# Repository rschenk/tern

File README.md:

# Tern

Terns are small white seabirds that can hover, but it's also a 30-key keyboard based on the [Hummingbird](https://github.com/PJE66/hummingbird)! Differences from the Hummigbird:

* Hot swappable
* Spaced for Chosfox CFX keycaps (tighter than normal choc spacing)
* Pinky keys are dropped down
* Thumbs are more reachy

I much prefer reachy thumbs vs tucky thumbs. Years of wiping out on skateboards means my right thumb doesn’t really make that tucking motion anymore.

The other deviation from the hummingbird is that I’m using the upper pinky key as my homerow. I’m using my pinky column as home and bottom rows, not top and home rows like the hummingbird does. Cognitively I like the hummingbird’s solution better, but after cutting a stack of cardboard prototypes, I just had to admit to myself that my pinky does not enjoy extending upwards.

## Case

There are laser cutting files for a case in `case`. The switch plate is made from 1/16" acrylic, and there is a 0.6mm silicone gasket sitting between it and the PCB. I don't actually think the switchplate does anything functional but it looks more finished. There is a file for cutting a sheet of self-adhesive foam for the back which really helps to dampen the sound. I used 1mm sticky backed EVA. 

## Firmware

This uses an identical matrix to the Hummingbird, so you can just lie to your firmware and tell it that it's a Hummingbird. As I mentioned, though, since I dropped the pinkies and use them as home-bottom, using the stock Hummingbird config will make your keymap look a bit strange. I've included a config for ZMK in `firmware/zmk` that tweaks the matrix mapping to allow your keymap to reflect the actual position of the keys.

## Build Guide

[Build guide and bill of materials are here](docs/build_guide.md)

## Want Sculpted Keycaps?

I designed this board for Chosfox CFX keycaps, which are 1mm narrower than standard Choc keycaps such as MBK. The CFX keycaps are great if you like flat uniform keycaps, but if you want something sculpted, I forked the Chicago Steno repo and resized them to fit the CFX spacing. They are also sprued so you can 3D print them from someplace like JLC. See [rschenk/cfx_chicago_stenographer](https://github.com/rschenk/cfx_chicago_stenographer)

## Thanks

* [Hummingbird](https://github.com/PJE66/hummingbird) for the original idea and matrix
* [Rufous](https://github.com/jcmkk3/trochilidae) for the basis of the Ergogen config and routing

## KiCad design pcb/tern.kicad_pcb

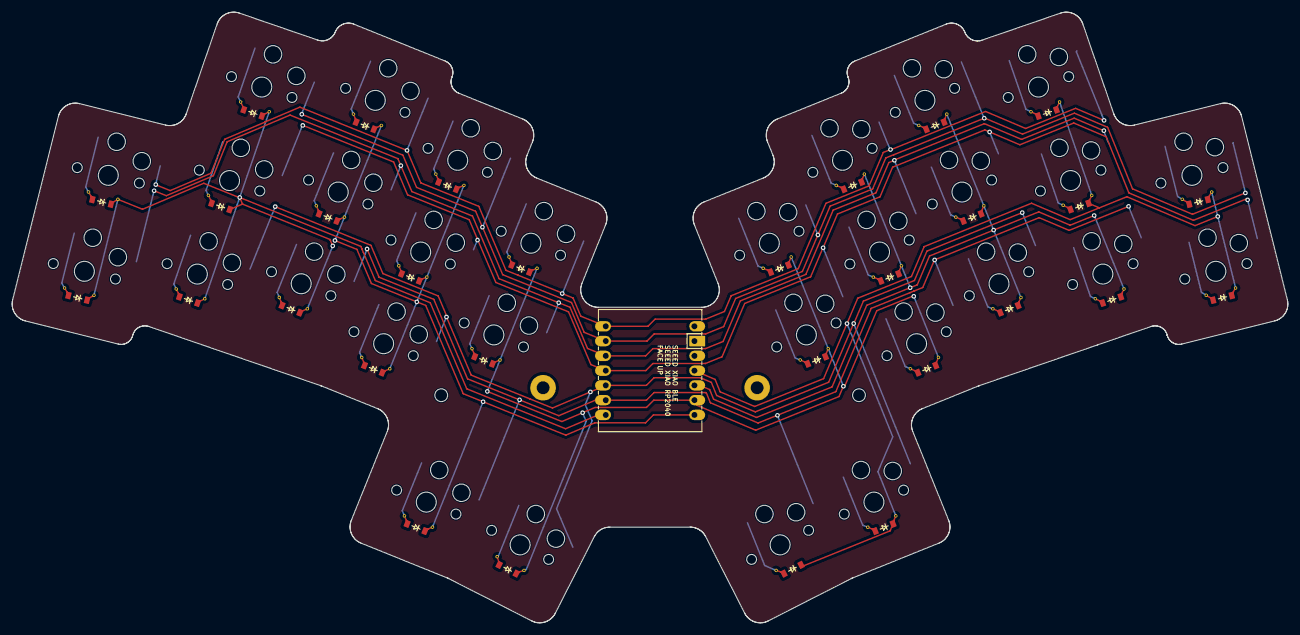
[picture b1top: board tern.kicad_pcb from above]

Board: 2 copper layers, 219.3 x 105.0 mm, 95 parts (0 on the bottom side), 41 nets.

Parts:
D1, D2, D3, D4, D5, D6, D7, D8, D9, D10, D11, D12, D13, D14, D15, D16, D17, D18, D19, D20, D21, D22, D23, D24, D25, D26, D27, D28, D29, D30: ComboDiode
MCU1: xiao-ble
PAD1, PAD2: MountingHole_2.2mm_M2
PAD3, PAD4: MountingHole_2.2mm_M2_Pad
S1, S2, S3, S4, S5, S6, S7, S8, S9, S10, S11, S12, S13, S14, S15, S16, S17, S18, S19, S20, S21, S22, S23, S24, S25, S26, S27, S28, S29, S30: PG1350
SB1, SB2, SB3, SB4, SB5, SB6, SB7, SB8, SB9, SB10, SB11, SB12, SB13, SB14, SB15, SB16, SB17, SB18, SB19, SB20, SB21, SB22, SB23, SB24, SB25, SB26, SB27, SB28, SB29, SB30: ChocBonusGoodies

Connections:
P0: MCU1.1, S2.2, S8.2, S13.2, S18.2, S24.2
P1: MCU1.2, S5.2, S11.2, S15.2, S21.2, S26.2
P2: MCU1.3, S1.2, S7.2, S12.2, S17.2, S23.2
P3: MCU1.4, S4.2, S10.2, S14.2, S20.2, S25.2
P4: MCU1.5, S3.2, S9.2, S19.2, S28.2, S29.2
P5: MCU1.6, S6.2, S16.2, S22.2, S27.2, S30.2
P6: D1.1, D1.3, D1.4, D2.1, D2.3, D2.4, D3.1, D3.3, D3.4, D4.1, D5.1, D5.3, D5.4, D6.1, D6.3, D6.4, MCU1.7
P7: D7.1, D7.3, D7.4, D8.1, D8.3, D8.4, D9.1, D9.3, D9.4, D10.1, D10.3, D10.4, D11.1, D11.3, D11.4, D27.1, D27.3, D27.4, MCU1.8
P8: D12.1, D12.3, D12.4, D13.1, D13.3, D13.4, D22.1, D22.3, D22.4, D25.1, D25.3, D25.4, D26.1, D26.3, D26.4, D28.1, D28.3, D28.4, MCU1.9
P9: D16.1, D16.3, D16.4, D19.1, D19.3, D19.4, D20.1, D20.3, D20.4, D21.1, D21.3, D21.4, D23.1, D23.3, D23.4, D24.1, D24.3, D24.4, MCU1.10
P10: D14.1, D14.3, D14.4, D15.1, D15.3, D15.4, D17.1, D17.3, D17.4, D18.1, D18.3, D18.4, D29.1, D29.3, D29.4, D30.1, MCU1.11
index_bottom: D9.2, D9.6, D9.7, S9.1
index_home: D10.2, D10.6, D10.7, S10.1
index_top: D11.2, D11.6, D11.7, S11.1
inner_home: D12.2, D12.6, D12.7, S12.1
inner_top: D13.2, D13.6, D13.7, S13.1
middle_bottom: D6.2, D6.6, D6.7, S6.1
middle_home: D7.2, D7.6, D7.7, S7.1
middle_top: D8.2, D8.6, D8.7, S8.1
mirror_index_bottom: D22.2, D22.6, D22.7, S22.1
mirror_index_home: D23.2, D23.6, D23.7, S23.1
mirror_index_top: D24.2, D24.6, D24.7, S24.1
mirror_inner_home: D25.2, D25.6, D25.7, S25.1
mirror_inner_top: D26.2, D26.6, D26.7, S26.1
mirror_middle_bottom: D19.2, D19.6, D19.7, S19.1
mirror_middle_home: D20.2, D20.6, D20.7, S20.1
mirror_middle_top: D21.2, D21.6, D21.7, S21.1
mirror_pinky_home: D14.2, D14.6, D14.7, S14.1
mirror_pinky_top: D15.2, D15.6, D15.7, S15.1
mirror_reachy_default: D30.2, D30.6, D30.7, S30.1
mirror_ring_bottom: D16.2, D16.6, D16.7, S16.1
mirror_ring_home: D17.2, D17.6, D17.7, S17.1
mirror_ring_top: D18.2, D18.6, D18.7, S18.1
mirror_tucky_default: D29.2, D29.6, D29.7, S29.1
pinky_home: D1.2, D1.6, D1.7, S1.1
pinky_top: D2.2, D2.6, D2.7, S2.1
reachy_default: D28.2, D28.6, D28.7, S28.1
ring_bottom: D3.2, D3.6, D3.7, S3.1
ring_home: D4.2, D4.6, D4.7, S4.1
ring_top: D5.2, D5.6, D5.7, S5.1
tucky_default: D27.2, D27.6, D27.7, S27.1

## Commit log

2023-07-19 Forgot to add Dockerfile
2023-07-19 Typo
2023-07-23 Fix too-tight switchplate on Xiao RP2040
    I had assumed that all Xiao boards were the same size, but actually the
    RP one is a little taller than the BLE and hit the switch plate.
2023-11-06 Fix a mis-named file
